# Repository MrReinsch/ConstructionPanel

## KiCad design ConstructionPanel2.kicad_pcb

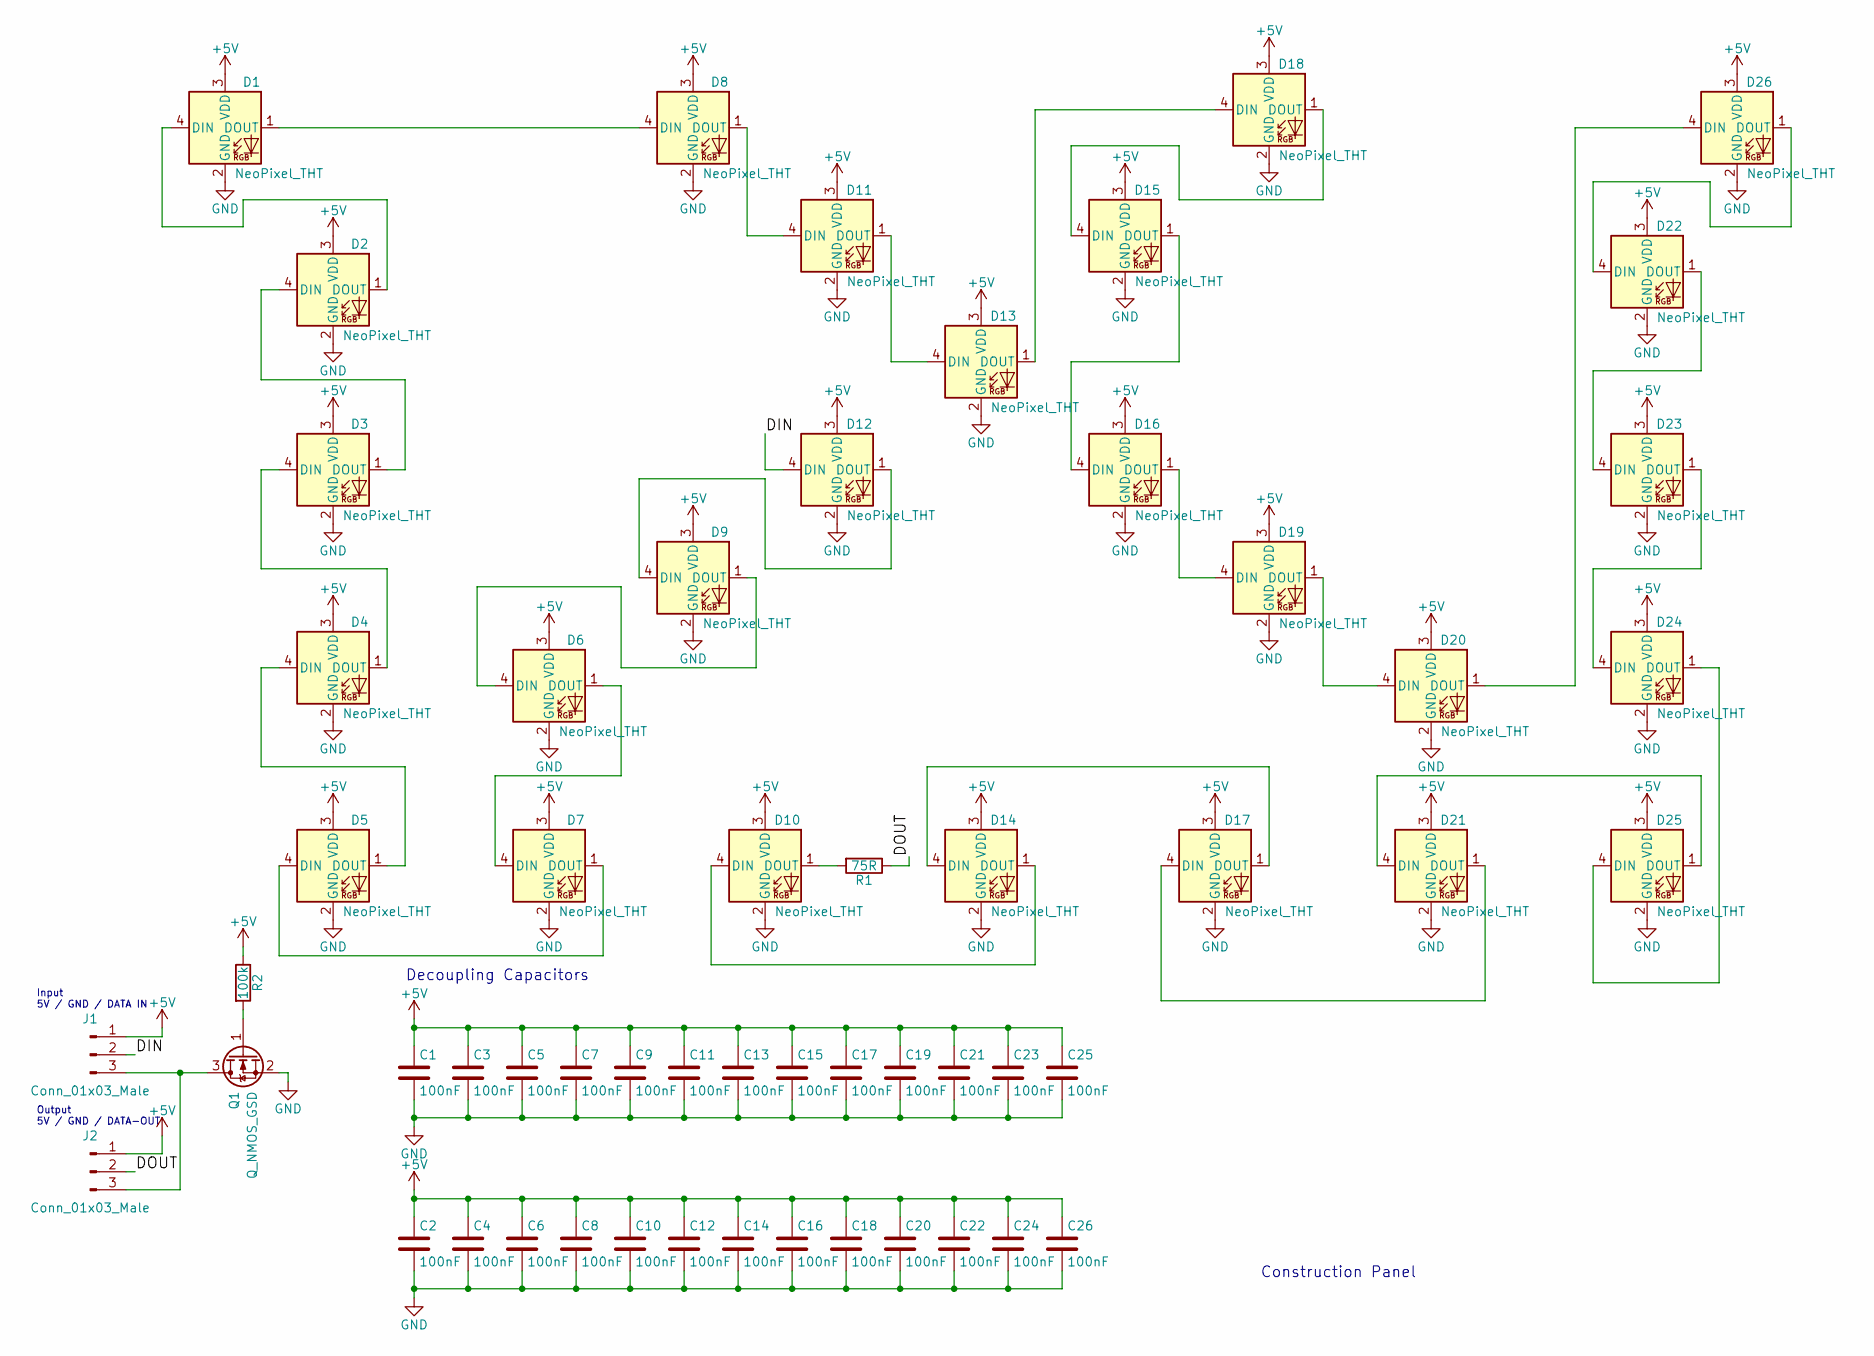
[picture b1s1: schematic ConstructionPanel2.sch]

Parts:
C1, C2, C3, C4, C5, C6, C7, C8, C9, C10, C11, C12, C13, C14, C15, C16, C17, C18, C19, C20, C21, C22, C23, C24, C25, C26: 100nF; C_0805_HandSoldering
D1, D2, D3, D4, D5, D6, D7, D8, D9, D10, D11, D12, D13, D14, D15, D16, D17, D18, D19, D20, D21, D22, D23, D24, D25, D26: NeoPixel_THT; LED_D5.0mm-4
J1, J2: Conn_01x03_Male; Pin_Header_Straight_1x03_Pitch2.54mm
Q1: Q_NMOS_GSD; SOT-23_Handsoldering
R1: 75R; R_0805_HandSoldering
R2: 100k; R_0805_HandSoldering

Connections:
+5V: C1.1, C2.1, C3.1, C4.1, C5.1, C6.1, C7.1, C8.1, C9.1, C10.1, C11.1, C12.1, C13.1, C14.1, C15.1, C16.1, C17.1, C18.1, C19.1, C20.1, C21.1, C22.1, C23.1, C24.1, C25.1, C26.1, D1.3 (VDD), D2.3 (VDD), D3.3 (VDD), D4.3 (VDD), D5.3 (VDD), D6.3 (VDD), D7.3 (VDD), D8.3 (VDD), D9.3 (VDD), D10.3 (VDD), D11.3 (VDD), D12.3 (VDD), D13.3 (VDD), D14.3 (VDD), D15.3 (VDD), D16.3 (VDD), D17.3 (VDD), D18.3 (VDD), D19.3 (VDD), D20.3 (VDD), D21.3 (VDD), D22.3 (VDD), D23.3 (VDD), D24.3 (VDD), D25.3 (VDD), D26.3 (VDD), J1.1, J2.1, R2.1
/DIN: D12.4 (DIN), J1.2
/DOUT: J2.2, R1.1
GND: C1.2, C2.2, C3.2, C4.2, C5.2, C6.2, C7.2, C8.2, C9.2, C10.2, C11.2, C12.2, C13.2, C14.2, C15.2, C16.2, C17.2, C18.2, C19.2, C20.2, C21.2, C22.2, C23.2, C24.2, C25.2, C26.2, D1.2 (GND), D2.2 (GND), D3.2 (GND), D4.2 (GND), D5.2 (GND), D6.2 (GND), D7.2 (GND), D8.2 (GND), D9.2 (GND), D10.2 (GND), D11.2 (GND), D12.2 (GND), D13.2 (GND), D14.2 (GND), D15.2 (GND), D16.2 (GND), D17.2 (GND), D18.2 (GND), D19.2 (GND), D20.2 (GND), D21.2 (GND), D22.2 (GND), D23.2 (GND), D24.2 (GND), D25.2 (GND), D26.2 (GND), Q1.2 (S)
unnamed: D1.1 (DOUT), D8.4 (DIN)
unnamed: D1.4 (DIN), D2.1 (DOUT)
unnamed: D2.4 (DIN), D3.1 (DOUT)
unnamed: D3.4 (DIN), D4.1 (DOUT)
unnamed: D4.4 (DIN), D5.1 (DOUT)
unnamed: D5.4 (DIN), D7.1 (DOUT)
unnamed: D6.1 (DOUT), D7.4 (DIN)
unnamed: D6.4 (DIN), D9.1 (DOUT)
unnamed: D10.1 (DOUT), R1.2
unnamed: D10.4 (DIN), D14.1 (DOUT)
unnamed: D11.1 (DOUT), D13.4 (DIN)
unnamed: D8.1 (DOUT), D11.4 (DIN)
unnamed: D9.4 (DIN), D12.1 (DOUT)
unnamed: D13.1 (DOUT), D18.4 (DIN)
unnamed: D14.4 (DIN), D17.1 (DOUT)
unnamed: D15.1 (DOUT), D16.4 (DIN)
unnamed: D15.4 (DIN), D18.1 (DOUT)
unnamed: D16.1 (DOUT), D19.4 (DIN)
unnamed: D17.4 (DIN), D21.1 (DOUT)
unnamed: D19.1 (DOUT), D20.4 (DIN)
unnamed: D20.1 (DOUT), D26.4 (DIN)
unnamed: D21.4 (DIN), D25.1 (DOUT)
unnamed: D22.1 (DOUT), D23.4 (DIN)
unnamed: D22.4 (DIN), D26.1 (DOUT)
unnamed: D23.1 (DOUT), D24.4 (DIN)
unnamed: D24.1 (DOUT), D25.4 (DIN)
unnamed: J1.3, J2.3, Q1.3 (D)
unnamed: Q1.1 (G), R2.2

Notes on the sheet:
Input 5V / GND / DATA IN
Output 5V / GND / DATA-OUT
Decoupling Capacitors
Construction Panel

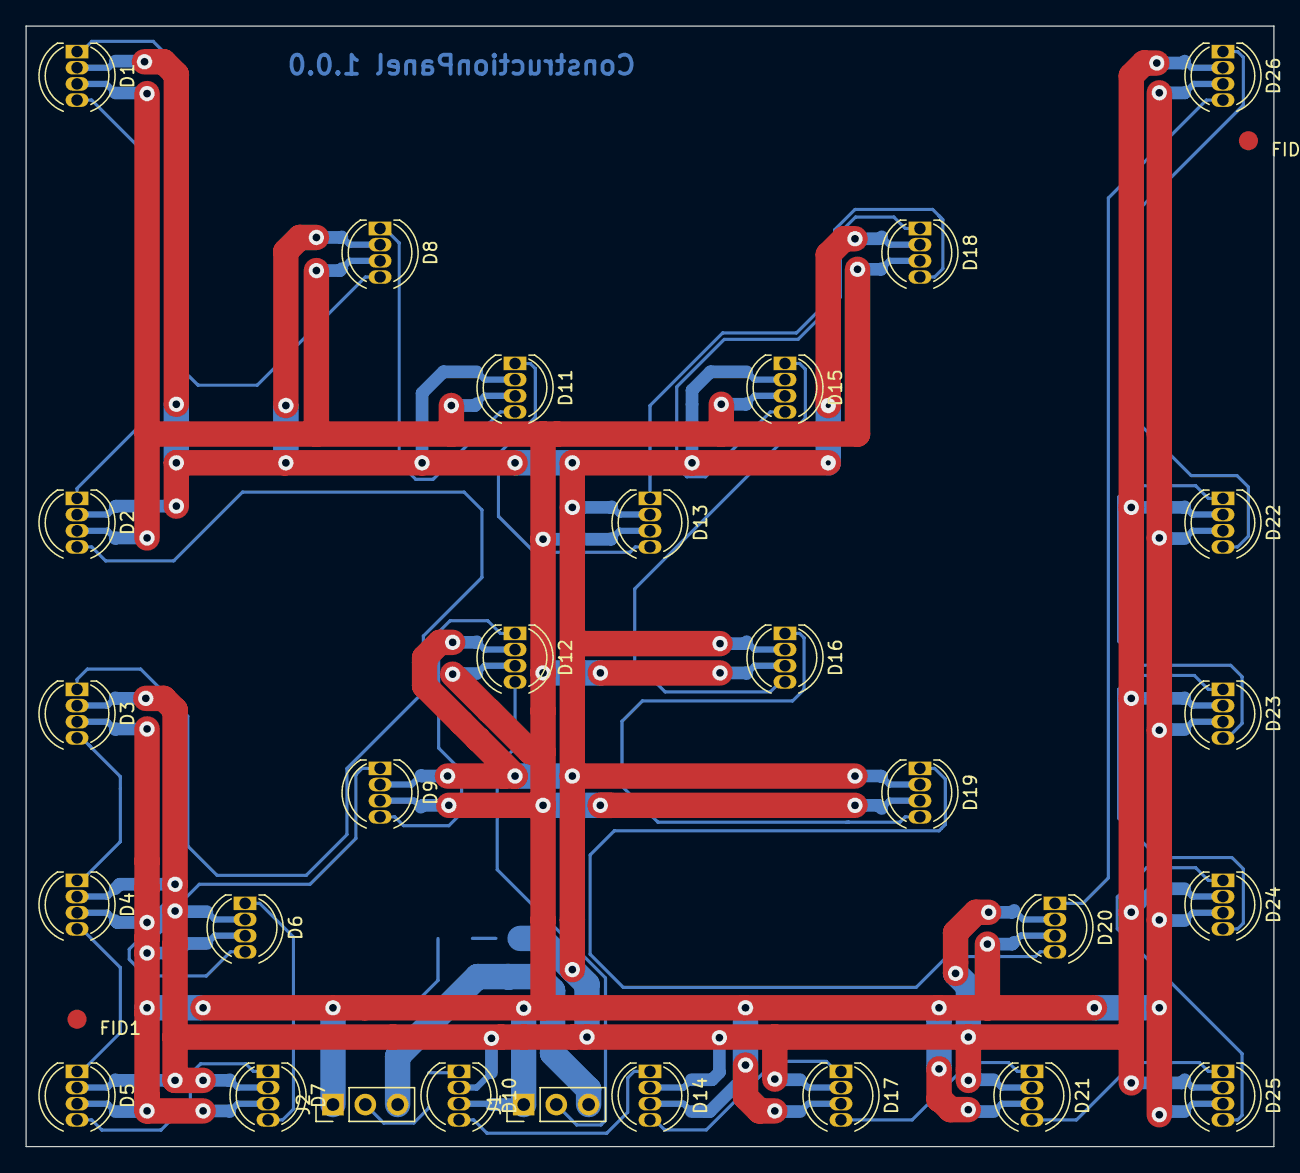
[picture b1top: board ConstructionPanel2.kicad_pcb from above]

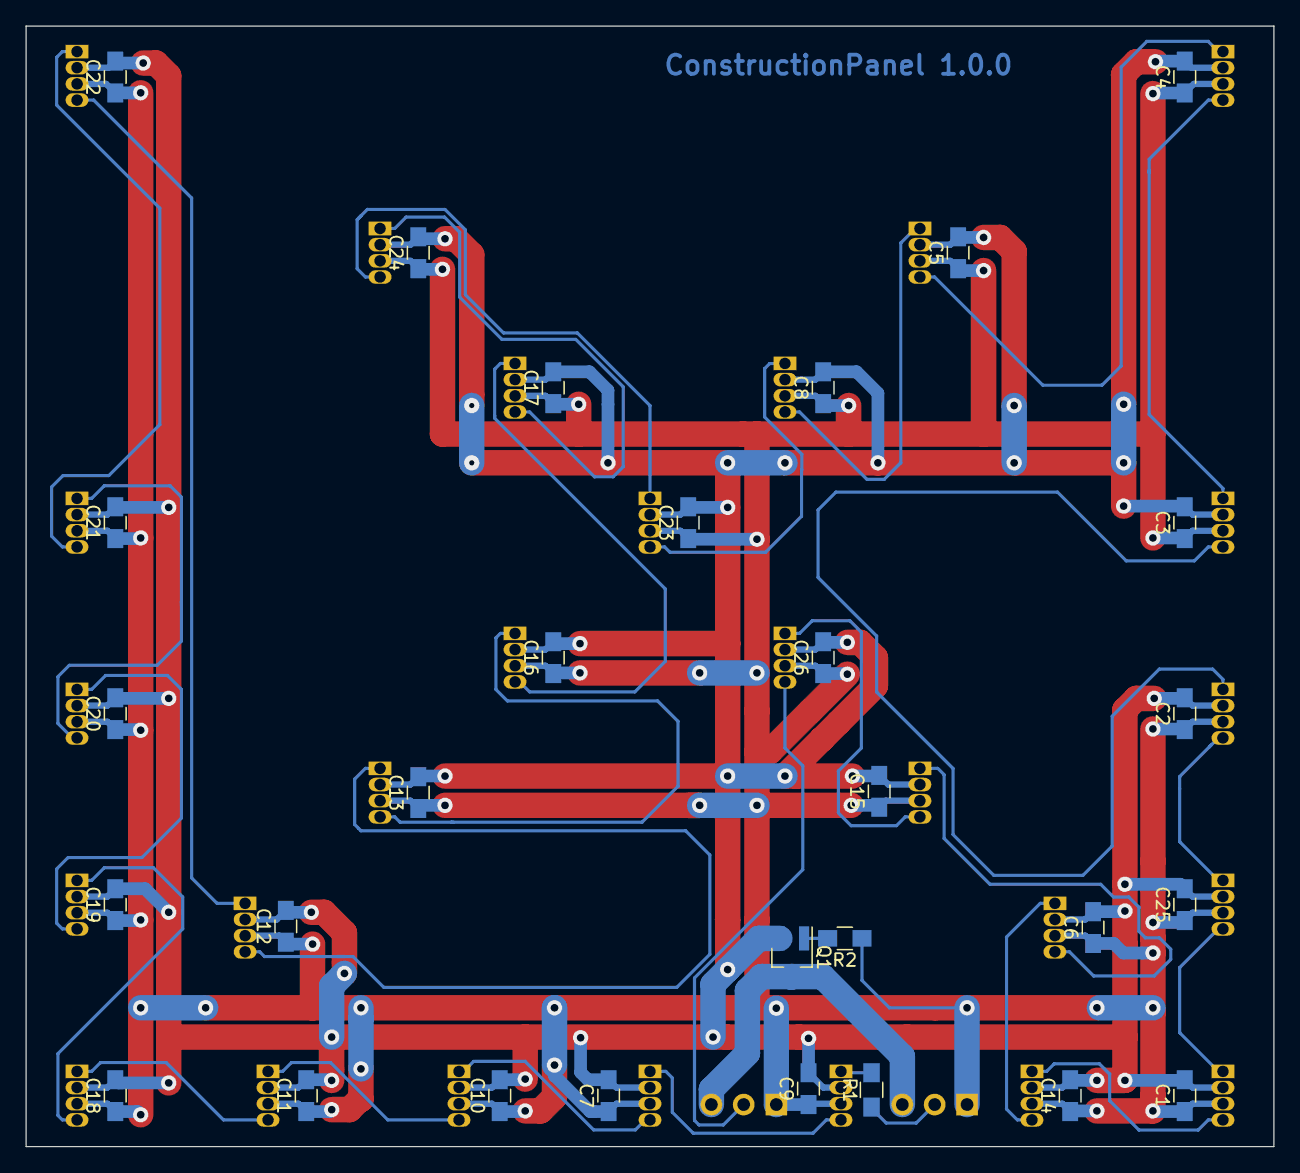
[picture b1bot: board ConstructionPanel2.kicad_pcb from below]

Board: 2 copper layers, 98.0 x 88.0 mm, 59 parts (29 on the bottom side), 32 nets.

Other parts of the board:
FID1, FID2: Fiducial_1mm_Dia_2.54mm_Outer_CopperTop

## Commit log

2019-03-19 first version
2019-03-21 change fiducial to 1.5
2019-03-22 via to 0.6 move connector
